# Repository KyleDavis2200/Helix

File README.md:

# Helix
Helix is an antweight ring spinner combat robot that uses its large weapon to protect itself from its opponents, instead of using normal armor.

# Features

* 10" asymmetric AR500 steel weapon spinning at over 260 MPH with 128 joules of energy!
* Vertical element to the weapon's counterweight blocks attacks from horizontal spinners before they hit the robot itself.
* Dual RS2205 Brushless Weapon Motors
* Tangent drive with tank treads.
* Carbon fiber frame
* Durable TPU body with ultra lightweight design.
* Custom PCB that serves as a switch, series board for the batteries, and a BEC for the receiver.

# Images

# Background

Combat robotics has been one of my main hobbies ever since I joined my school's combat robotics team at the beginning fot he 2023-2024 school year. Throughout that time, I have mainly spent my time building 15lb eggbeater combat robots, where, due to the time and money invested into them, we are often scared to go too far outside of the box since a small design flaw could mean thousands of dollars and hundreds of hours were wasted. Highway is the perfect opportunity to make something outside of the box, as complex and creative projects are rewarded. 

# Bill of Materials

|Item                         |Individual Cost|Quantity      |Total Cost (Includes shipping)|Notes                                                                                                                                                                   |
|-----------------------------|---------------|--------------|------------------------------|-------------------------------------------------------------------------------------------------------------------------------------------------------------------------|
|Drive Motor Screw            |8.75           |1 (pack of 25)|8.75                          |*Only 8 in the robot                                                                                                                                                     |
|Drive Standoff/WM Screw      |6.4            |30            |6.4                           |*Ordering extra screws in case some get lost or damaged. 24 are used in the robot.                                                                                       |
|Main Screw                   |4.36           |12            |4.36                          |*Ordering extra screws in case some get lost or damaged. 8 are used in the robot.                                                                                        |
|M3 Plastite                  |5.69           |1(Pack of 25) |5.69                          |*Only 6 in the robot                                                                                                                                                     |
|4in1 ESC                     |38.8           |1             |38.8                          |                                                                                                                                                                         |
|PCB                          |9.62           |1             |9.62                          |                                                                                                                                                                         |
|Battery                      |9.25           |2             |18.5                          |*Need 2 because the robot uses 2 at once                                                                                                                                 |
|Carbon Fiber Parts           |29.1           |1             |29.1                          |                                                                                                                                                                         |
|Weapon                       |18.47          |2             |36.94                         |*Only 1 is used in the robot, other is a spare                                                                                                                           |
|Bearing Washer               |0.77           |5             |3.85                          |*4 are used in the robot, 5th is a spare                                                                                                                                 |
|Weapon Bearing               |12.99          |1 (Pack of 10)|12.99                         |*4 are used in the robot                                                                                                                                                 |
|Standoff                     |3.06           |1 (Pack of 5) |3.06                          |*4 are used in the robot                                                                                                                                                 |
|Drive Standoff               |8.99           |1 (Pack of 10)|8.99                          |*8 are used in the robot                                                                                                                                                 |
|Repeat Tangent Drive Motor   |22.5           |2             |45                            |*2 are used in the robot                                                                                                                                                 |
|RS2205 Weapon Motor          |7.6            |2             |15.2                          |*2 are used in the robot                                                                                                                                                 |
|XR2 Receiver                 |9.99           |1             |9.99                          |                                                                                                                                                                         |
|Digikey                      |18.54          |1             |18.54                         |*1x AP7381-50SA-7, 1x 2.2 uF 0805 Ceramic Cap, 1x 1 uF 0805 Ceramic Cap, 3x XT30 used on PCB, bought some extras because I'm new to soldering and am scared to mess it up|
|                             |               |              |                              |                                                                                                                                                                         |
|8x M3 Washer                 |N/A            |N/A           |N/A                           |*Already Have                                                                                                                                                            |
|M5 x 12mm Screw              |N/A            |N/A           |N/A                           |*Already Have                                                                                                                                                            |
|2x M5 Nut                    |N/A            |N/A           |N/A                           |*Already Have                                                                                                                                                            |
|M5 Washer                    |N/A            |N/A           |N/A                           |*Already Have                                                                                                                                                            |
|M3 Screw for Switch          |N/A            |N/A           |N/A                           |*Already Have                                                                                                                                                            |
|M3 Nut for Switch            |N/A            |N/A           |N/A                           |*Already Have                                                                                                                                                            |
|2x M2 Screws for PCB Mounting|N/A            |N/A           |N/A                           |*Already Have                                                                                                                                                            |
|2x M2 Screws for PCB Mounting|N/A            |N/A           |N/A                           |*Already Have                                                                                                                                                            |
|PLA Filament                 |N/A            |N/A           |N/A                           |*Already Have                                                                                                                                                            |
|TPU Filament                 |N/A            |N/A           |N/A                           |*Already Have                                                                                                                                                            |
|Nylon Filament               |N/A            |N/A           |N/A                           |*Already Have                                                                                                                                                            |
|                             |               |              |                              |                                                                                                                                                                         |
|Battery Charger              |N/A            |N/A           |N/A                           |*Planning to buy myself                                                                                                                                                  |
|Transmitter                  |N/A            |N/A           |N/A                           |*Planning to buy myself because I want something a little nicer than what would be fair to buy from Hack Club's money                                                    |
|                             |               |              |                              |                                                                                                                                                                         |
|Testing Cage                 |N/A            |N/A           |N/A                           |*Have access to one through my school's combat robotics team                                                                                                             |
|                             |               |              |                              |                                                                                                                                                                         |
|                             |               |              |                              |                                                                                                                                                                         |
|Total                        |N/A            |N/A           |275.78                        |                                                                                                                                                                         |

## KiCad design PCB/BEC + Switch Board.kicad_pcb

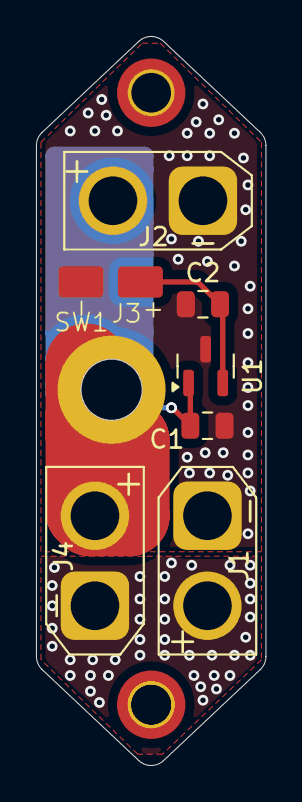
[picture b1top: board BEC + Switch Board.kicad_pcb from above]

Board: 2 copper layers, 12.8 x 40.5 mm, 8 parts (1 on the bottom side), 4 nets.

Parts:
C1: 1uF; C_0805_2012Metric
C2: 2.2uF; C_0805_2012Metric
J1, J2, J4: Conn_01x02_Socket; AMASS_XT30U-M_1x02_P5.0mm_Vertical
J3: Conn_01x02_Socket; SignalWirePads
SW1: SW_DIP_x01; Screw Switch
U1: AP7381-50SA-7; SOT-23

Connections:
/GND: C1.1, C2.1, J1.2, J2.2, J3.2, U1.3 (GND)
unnamed: J1.1, J4.2
unnamed: C1.2, J2.1, U1.1 (VI)
unnamed: C2.2, J3.1, U1.2 (VO)

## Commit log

2025-06-14 Rename image_2025-06-13_205627015.png to Images/image_2025-06-13_205627015.png
2025-06-14 Rename image.png to bearingsketch.png
2025-07-16 Create a
